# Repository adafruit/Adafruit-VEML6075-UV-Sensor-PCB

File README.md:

## Adafruit VEML6075 UVA UVB and UV Index Sensor Breakout PCB

<a href="http://www.adafruit.com/products/3964"><br/>
Click here to purchase one from the Adafruit shop</a>

PCB files for the Adafruit VEML6075 UVA UVB and UV Index Sensor Breakout. Format is EagleCAD schematic and board layout
* https://www.adafruit.com/product/3964

### Description

This little sensor is a great way to add UVA and UVB light sensing to any microcontroller project. The VEML6075 from Vishay has both true UVA and UVB band light sensors and an I2C-controlled ADC that will take readings and integrate them. The sensor also comes with calibration registers so you can easily convert the UVA/UVB readings into the UV Index.

Compared to our other UV sensors, this one actually does a pretty good job of getting accurate UV data. Unlike the Si1145, it has a real UV sensor, and in contrast to the VEML6070, it has dual band senors and an Index calculation algorithm. So far this is the best UV sensor we've got!

This UV sensor works great with 3 or 5V power or logic, its nice and compact, and its easy to use with any I2C-capable microcontroller. We have [example code and libraries for Arduino](https://github.com/adafruit/Adafruit_VEML6075) and [CircuitPython/Python](https://github.com/adafruit/Adafruit_CircuitPython_VEML6075).

Each order comes with one assembled PCB with a sensor, power regulator, level shifting and a small piece of header. Some light soldering is required to attach the header but it's a fast task!

### License

Adafruit invests time and resources providing this open source design, please support Adafruit and open-source hardware by purchasing products from [Adafruit](https://www.adafruit.com)!

Designed by Limor Fried/Ladyada for Adafruit Industries.

Creative Commons Attribution/Share-Alike, all text above must be included in any redistribution. See license.txt for additional details.

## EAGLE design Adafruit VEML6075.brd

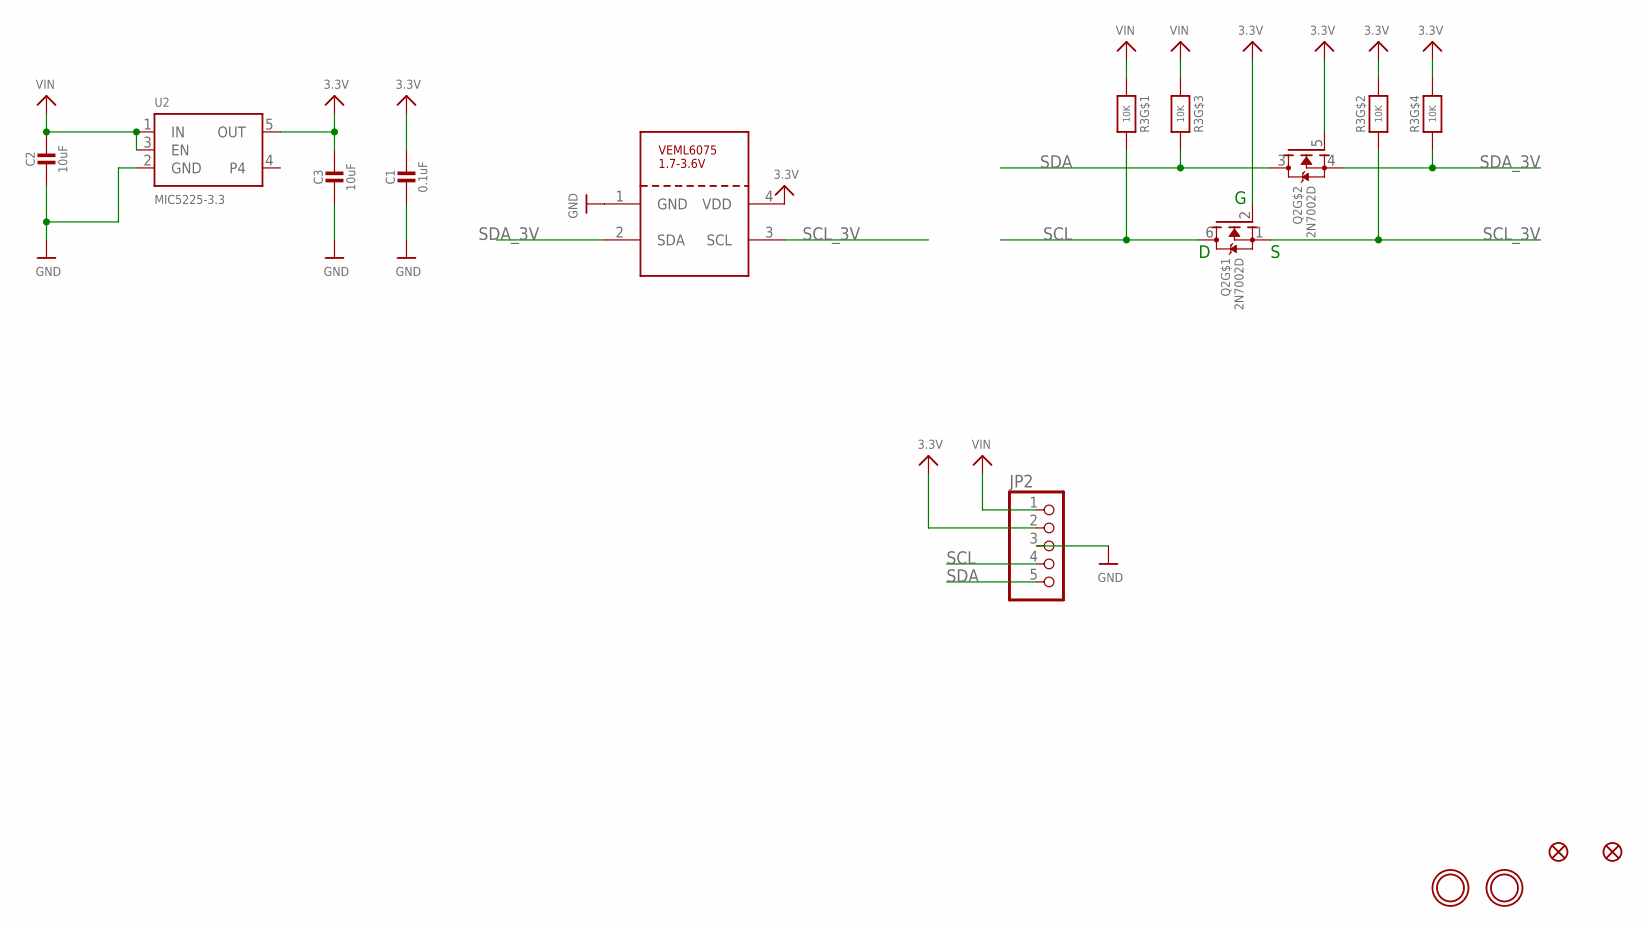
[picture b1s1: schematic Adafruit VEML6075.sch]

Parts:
C1: 0.1uF; 0603-NO
C2, C3: 10uF; 0805-NO
FID1, FID2: FIDUCIAL_1MM
JP2: HEADER-1X5ROUND; 1X05_ROUND
Q2: 2N7002D; SOT363
R3: 10K; RESPACK_4X0603
U2: MIC5225-3.3; SOT23-5
U$3, U$4: MOUNTINGHOLE2.5; MOUNTINGHOLE_2.5_PLATED
U$12: VEML6075

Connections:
3.3V: C1.1, C3.1, JP2.2, Q2.2 (G), Q2.5 (G), R3.2 (1), R3.4 (1), U2.5 (OUT), U$12.4 (VDD)
GND: C1.2, C2.2, C3.2, JP2.3, U2.2 (GND), U$12.1 (GND)
SCL: JP2.4, Q2.6 (D), R3.8 (2)
SCL_3V: Q2.1 (S), R3.7 (2), U$12.3 (SCL)
SDA: JP2.5, Q2.3 (D), R3.6 (2)
SDA_3V: Q2.4 (S), R3.5 (2), U$12.2 (SDA)
VIN: C2.1, JP2.1, R3.1, R3.3 (1), U2.1 (IN), U2.3 (EN)

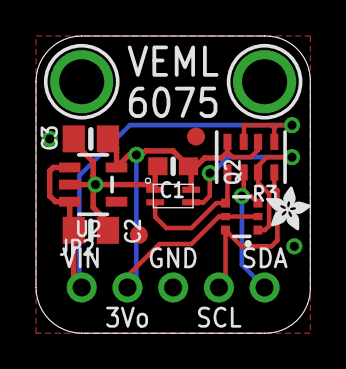
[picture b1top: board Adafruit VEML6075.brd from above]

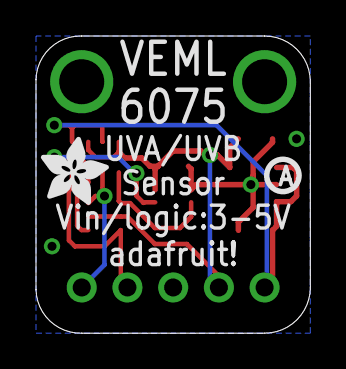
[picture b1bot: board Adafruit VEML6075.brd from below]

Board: 2 copper layers, 15.2 x 16.5 mm, 15 parts (2 on the bottom side), 7 nets.

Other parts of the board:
U$1: ADAFRUIT_3.5MM
U$8: ADAFRUIT_2.5MM
U$27: PCBFEAT-REV-040

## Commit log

2018-09-26 init
2019-07-16 updated to use cookiecutter for pcb repos

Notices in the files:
parts and their libraries:
microbuilder: This work is placed in the public domain, and may be freely used for commercial and non-commercial work with the following conditions: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
